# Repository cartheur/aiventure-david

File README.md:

## aiventure-david

Most complex implementation of the animals and emotional toys interactive codebases. A directly-embodied form is [joi](https://github.com/cartheur-joi/arthur-bipedal). Source code in-process of development where our specialized RL rules

* [ideal](https://github.com/cartheur/ideal)
* [haden](https://github.com/ai-haden/aiventure-haden).

_Background_

This project is a 3D-Printed bipedal robot that servers as a platform for _aeon_. It is the third-generation and the most ambitious of our embodied works. The project evolved from:

* The smartphone (2005 - 2016)
* A [toy bear](https://github.com/cartheur/henry) (2016 - 2018)
* A [Nao implementation](https://rumble.com/c/c-2434744) purely as an _aeon personality_ (2017 - 2020)
* A plush [emotional toy](https://emotional.toys) (2017 - 2019)
* An environmentally-friendly [bipedal robot](https://github.com/cartheur/aiventure-david) (2020 - Present)

Here is what it sees

And is evolving into:

* Head redesign for the bipedal robot using the native code files from Poppy but advancing using Solidworks. This head will encapsulate a Liva minicomputer. (Started October 2022)
* Battery compartment and battery to remove the plugged-in power supply. It does run on a 40Ah cell but is pretty power thirsty, even while idle. (Scheduled October 2023)
* De-evolution to a 4.3" HDMI touch screen to link with odroid XU-4, sold by [waveshare](https://www.waveshare.com/4.3inch-HDMI-LCD-B.htm)
    - Problem is: The screen is bloody annoying as it seems to splay one's face with juicy radiation. I was right not considering these kinds of interfaces previously. Bipedal only has a camera and this will stay for the moment. (April 2024)
    - People shoudn't (and certainly aren't) fucking spoiled about a robot having a face. Show me one in manufacture or proposal _right now_.

The complexity of behaviour and implementation is arbitrary. Here at the Generation-Three of the work, currently what is necessary is a stationary test as I complete some animation-training code. I will describe this is in greater detail later. Key is to be able to create my own stuctures and application behaviours outside of the dictations of a compiler - herein lies the direct challenge.

Here is it running (on battery) taking a picture of m.e.

As it is stupid to have a bipedal robot friend attached to cables, the david prototype is at the point where I am starting to test operation with a battery. This battery is rather large (200mm x 150mm x 30mm) at 1.16kg but will run 12 volts to a level of 40Ah. Stationary tests indicate the battery will last 2.5 hours but the next steps will be standing and animation training tests.

As I did work on wireless power, it is a feature to leverage a wireless-charged battery so that the battery could be, say, in a backpack and recharged with a pad, rather than cables. There are some manufacturers working on this but currently it is just wireless-powering phones. Time will tell!

### What does the name of the project mean?

The term *aiventure* means "adventure in AI". The addition of the suffix *david* I don't readily recall, but it is between one of these three _davids_, although it could be more conspiratorial than that:

This david,...

this david, or,...

this david.

#### Errata

Apart from narratives that exclude everyone from building, the build is the thing and the thing alone.

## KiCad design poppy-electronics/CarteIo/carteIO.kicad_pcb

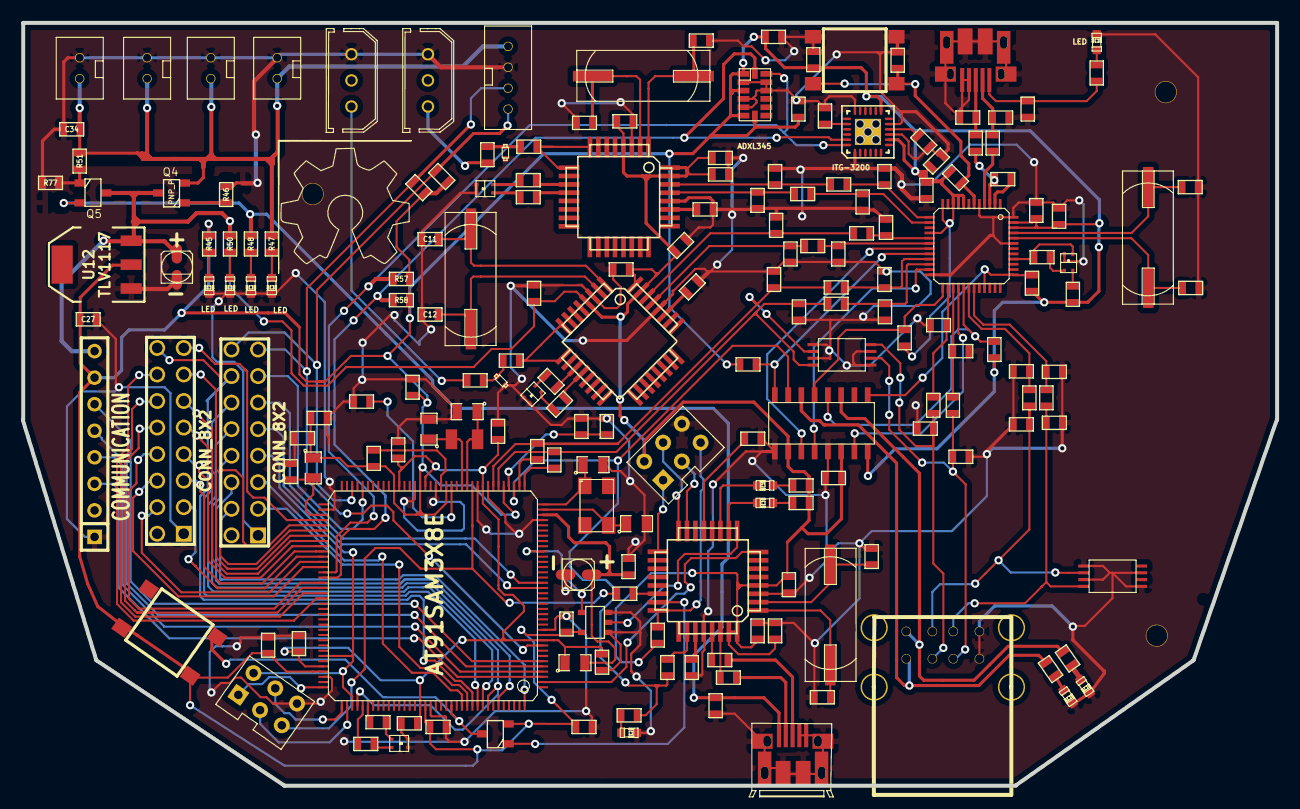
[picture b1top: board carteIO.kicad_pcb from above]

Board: 2 copper layers, 120.0 x 73.0 mm, 195 parts (0 on the bottom side), 156 nets.

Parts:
C1, C2, C61, C62: 22p; SM0603_Capa
C3, C5: 27p; SM0603_Capa
C4, C16, C19, C37, C42, C43, C44, C45, C46, C47, C48, C49, C50, C51, C52, C53, C54, C64, C65, C66, C67, C71: 100n; SM0603_Capa
C6, C7, C8, C9, C14, C15, C17, C20, C28, C29, C59: 22pF; SM0603_Capa
C10, C55: 10u; CAN_RADIAL-CMS
C11, C12, C21, C22: 18p; SM0603_Capa
C13, C23, C38, C63: 1u; SM0603_Capa
C18, C24, C34, C35, C36, C68, C69, C70: 4.7u; SM0603_Capa
C25, C26: 0.1u; SM0603_Capa
C27: 22uF; SM0603_Capa
C39: 10n 4V; SM0603_Capa
C40: 100n 4V; SM0603_Capa
C41: 2.2n 50V; SM0603_Capa
C56, C57, C58, C60: 4.7p; SM0805
C72: 100n 2V; SM0603_Capa
D1, D11: 5.1V; VMD2
D2, D3, D4, D5, D6, D10, D12, D13, D14, D15: LED; LED-0603
FB1, FB2: FILTER; SM0805
J1, J2: UUSB; microUSB
K1, K2: CONN_3; Molex-3-Broches
P1, P4, P5, P9: CONN_2; JST2_TV
P2, P3: CONN_6; HE10-6C
P6, P7: CONN_8X2; pin_array_8x2
P8: COMMUNICATION; SIL-8
P10: CONN_4; JST4_TV
Q1, Q2: 16MHz; HC-49
Q3: 6MHz; HC-49
Q4, Q5: PNP_P; SOT23
Q6: MOS_P2; SOT23
R1, R2, R5, R6, R7, R8, R9, R10, R17, R18, R33, R34: 27R; SM0603
R3: 1.5k; SM0603
R4, R54, R65, R67, R68: 10k; SM0603
R11, R12, R21, R22, R35, R36: R; SM0603
R13, R15, R16, R23, R25, R26, R45: 150; SM0603
R19, R20, R27, R28, R29, R30, R31, R32, R39, R40: 15k; SM0603
R46, R51, R66: 1k; SM0603
R47, R48, R49, R50, R71, R72, R73, R75, R76: 330; SM0603
R52, R53: 39R 1%; SM0603
R55, R56, R57, R58: 2.2k; SM0603
R59: 0; SM0603
R62: 6k8 1%; SM0603
R63, R64, R69, R70: 22R; SM0603
R77: 100k; SM0603
SAM3X8E1: AT91SAM3X8E; LQFP144
SW1, SW2: SW_PUSH; SW_PUSH_SMD
TH1, TH11: 100; SM0603
U1, U3: ATMEGA32U2; TQFP32
U2, U4, U10, U20: LED-BICOLORE; Led_Bicolore
U5: TUSB2077; LQFP48_perso
U6: TPS2044; SOIC16
U8, U9: SN75240; TSSOP8
U11: USB*2
U12: TLV1117; SOT223
U14: ITG-3200; QFN24
U18: ATMEGA16U2; TQFP32
U19: SN74LVC1G125; SOT23-5
U21: ADXL345; LGA14
X1: 12MHz; CRYSTAL_ABM3C
X2: 32kHz; CM315
X3: 16MHz; HC-49
hole-2mm, hole-2mm#2, hole-2mm#3: VAL**; hole-2mm

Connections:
/Alim/3.3V: C27.1, C37.1, C38.1, C39.1, C40.1, C42.1, C43.1, C44.1, C46.1, C47.1, C49.1, C67.1, C68.1, C69.1, C70.1, FB1.1, P8.7, Q6.2, R4.2, R11.2, R12.2, R21.2, R22.2, R36.1, R45.1, R54.1, R55.2, R56.2, R57.2, R58.2, SAM3X8E1.11, SAM3X8E1.41, SAM3X8E1.52, SAM3X8E1.57, SAM3X8E1.62, SAM3X8E1.105, SAM3X8E1.125, SW2.2, U5.8, U5.9, U5.10, U5.12, U5.16, U5.46, U5.47, U6.8, U12.2, U14.8, U14.13, U19.5, U21.1, U21.3, U21.6, U21.7
/Alim/5V: C10.1, C16.1, C18.1, C19.1, C24.1, C25.1, C26.1, C64.1, C65.1, C66.1, C71.1, P3.2, P8.8, Q4.3, Q5.3, R50.1, R65.1, R69.1, R70.1, U1.4, U1.31, U1.32, U3.4, U3.31, U3.32, U6.2, U6.6, U12.3, U18.4, U18.31, U18.32
/Arduino/AI0: P7.13, SAM3X8E1.78
/Arduino/AI1: P7.11, SAM3X8E1.79
/Arduino/AI2: P7.9, SAM3X8E1.80
/Arduino/AI3: P7.7, SAM3X8E1.81
/Arduino/AI4: P7.5, SAM3X8E1.82
/Arduino/AI5: P7.3, SAM3X8E1.83
/Arduino/AI6: P7.4, SAM3X8E1.84
/Arduino/AI7: P7.6, SAM3X8E1.85
/Arduino/AI8: P7.8, SAM3X8E1.88
/Arduino/AI9: P7.10, SAM3X8E1.89
/Arduino/AI10: P7.12, SAM3X8E1.90
/Arduino/AI11: P7.14, SAM3X8E1.91
/Arduino/AVREF: C52.1, FB1.2, SAM3X8E1.75
/Arduino/D+: R9.2, R29.1, R53.1, SAM3X8E1.42, U8.8
/Arduino/D+prog: J2.3, R63.1
/Arduino/D-: R10.2, R30.1, R52.1, SAM3X8E1.43, U8.6
/Arduino/D-prog: J2.2, R64.2
/Arduino/DAC0: P7.15, SAM3X8E1.76
/Arduino/DAC1: P7.16, SAM3X8E1.77
/Arduino/ERASE: Q6.3, SAM3X8E1.130, SW2.1
/Arduino/LED1: R76.1, SAM3X8E1.113
/Arduino/LED2: R75.1, SAM3X8E1.114
/Arduino/MISO: P2.1, SAM3X8E1.108
/Arduino/MOSI: P2.4, SAM3X8E1.109
/Arduino/NCPSO: P2.2, P6.7, SAM3X8E1.102, SAM3X8E1.111
/Arduino/PWM2: P6.4, SAM3X8E1.144
/Arduino/PWM3: P6.6, SAM3X8E1.139
/Arduino/PWM4: P6.8, SAM3X8E1.112, SAM3X8E1.137
/Arduino/PWM5: P6.10, SAM3X8E1.136
/Arduino/PWM6: P6.12, SAM3X8E1.135
/Arduino/PWM7: P6.14, SAM3X8E1.134
/Arduino/PWM8: P6.3, SAM3X8E1.133
/Arduino/PWM9: P6.5, SAM3X8E1.132
/Arduino/PWM11: P6.9, SAM3X8E1.20
/Arduino/PWM12: P6.11, SAM3X8E1.21
/Arduino/PWM13: P6.13, SAM3X8E1.68
/Arduino/PWR: R66.1, R71.1, SAM3X8E1.39, U6.15
/Arduino/RX1: P8.3, SAM3X8E1.3
/Arduino/RX2: P8.5, SAM3X8E1.5
/Arduino/SCL: R58.1, SAM3X8E1.87, U14.23, U21.14
/Arduino/SCLK: P2.3, SAM3X8E1.110
/Arduino/SDA: R57.1, SAM3X8E1.86, U14.24, U21.13
/Arduino/TST: R59.1, SAM3X8E1.51
/Arduino/TX1: P8.4, SAM3X8E1.4
/Arduino/TX2: P8.6, SAM3X8E1.6
/Arduino/VBG: C59.1, R62.1, SAM3X8E1.40
/Arduino/VDDOUT: C45.1, C48.1, C50.1, C51.1, C53.1, FB2.1, SAM3X8E1.10, SAM3X8E1.45, SAM3X8E1.56, SAM3X8E1.61, SAM3X8E1.104, SAM3X8E1.124
/Arduino/VDDPLL: C54.1, C55.1, FB2.2, SAM3X8E1.34
/Arduino/XIN: C56.1, SAM3X8E1.36, X1.1
/Arduino/XIN32: C58.1, SAM3X8E1.48, X2.1
/Arduino/XOUT: C57.1, SAM3X8E1.35, X1.3
/Arduino/XOUT32: C60.1, SAM3X8E1.49, X2.2
/Arduino/programmation/EraseCMD: Q6.1, U18.23
/Arduino/programmation/MISO: P3.1, U18.17
/Arduino/programmation/MOSI: P3.4, U18.16
/Arduino/programmation/RX ATMEGA: SAM3X8E1.2, U18.8
/Arduino/programmation/Reset: P3.5, R65.2, U18.24
/Arduino/programmation/ResetCMD: P2.5, R67.1, SAM3X8E1.47
/Arduino/programmation/SCK: P3.3, U18.15
/Arduino/programmation/TX ATMEGA: SAM3X8E1.27, U19.4
/USB2AX2/D+1: R5.2, R19.1, U1.29
/USB2AX2/D-1: R6.2, R20.1, U1.30
/USB2AX/D+: R7.2, R27.1, U3.29
/USB2AX/D-: R8.2, R28.1, U3.30
/USBHUB/D+hub: C1.1, J1.3, R1.1
/USBHUB/D-hub: C2.1, J1.2, R2.1
/USBHUB/USBFilter/DM0: R2.2, U5.4
/USBHUB/USBFilter/DM1: C7.1, R6.1, U5.13
/USBHUB/USBFilter/DM2: C9.1, R8.1, U5.17
/USBHUB/USBFilter/DM3: C15.1, R10.1, U5.21
/USBHUB/USBFilter/DM4: C20.1, R18.1, U5.26
/USBHUB/USBFilter/DM5: C29.1, R34.1, U5.30
/USBHUB/USBFilter/DP0: R1.2, R3.2, U5.3
/USBHUB/USBFilter/DP1: C6.1, R5.1, U5.14
/USBHUB/USBFilter/DP2: C8.1, R7.1, U5.18
/USBHUB/USBFilter/DP3: C14.1, R9.1, U5.22
/USBHUB/USBFilter/DP4: C17.1, R17.1, U5.27
/USBHUB/USBFilter/DP5: C28.1, R33.1, U5.31
/USBHUB/hubstatus: R35.1, U5.40, U10.4
/connector out/5V: C34.1, P1.1, P4.1, P5.1, P9.1, P10.1, Q4.2, R47.1, R51.1
/connector out/D+Bot: R33.2, R39.1, U9.8, U11.6
/connector out/D+Top: R17.2, R31.1, U8.2, U11.5
/connector out/D- Top: R18.2, R32.1, U8.4, U11.3
/connector out/D-Bot: R34.2, R40.1, U9.6, U11.4
/connector out/PWR Bot: R73.1, U6.11, U11.2
/connector out/PWR Top: R72.1, U6.14, U11.1
/connector out/SCL: P6.16, P10.4, R56.1, SAM3X8E1.70
/connector out/SDA: P6.15, P10.3, R55.1, SAM3X8E1.9
/connectorIn/Vhub: C36.1, J1.1, R49.1
/connectorIn/Vprog: C35.1, J2.1, Q5.2, R48.1
GND: C1.2, C2.2, C3.2, C4.1, C5.2, C6.2, C7.2, C8.2, C9.2, C10.2, C11.2, C12.2, C13.2, C14.2, C15.2, C16.2, C17.2, C18.2, C19.2, C20.2, C21.2, C22.2, C23.2, C24.2, C25.2, C26.2, C27.2, C28.2, C29.2, C34.2, C35.2, C36.2, C37.2, C38.2, C39.2, C40.2, C41.2, C42.2, C43.2, C44.2, C45.2, C46.2, C47.2, C48.2, C49.2, C50.2, C51.2, C52.2, C53.2, C54.2, C55.2, C56.2, C57.2, C58.2, C59.2, C60.2, C61.2, C62.2, C63.2, C64.2, C65.2, C66.2, C67.2, C68.2, C69.2, C70.2, C71.2, C72.2, D1.1, D2.2, D3.2, D4.2, D5.2, D6.2, D11.1, D13.2, D14.2, D15.2, J1.4, J1.5, J2.4, J2.5, K1.1, K2.1, P1.2, P2.6, P3.6, P4.2, P5.2, P6.1, P7.1, P8.1, P9.2, P10.2, R19.2, R20.2, R27.2, R28.2, R29.2, R30.2, R31.2, R32.2, R39.2, R40.2, R46.2, R59.2, R62.2, R68.1, R77.2, SAM3X8E1.12, SAM3X8E1.33, SAM3X8E1.44, SAM3X8E1.46, SAM3X8E1.54, SAM3X8E1.58, SAM3X8E1.74, SAM3X8E1.106, SAM3X8E1.126, SW1.1, U1.3, U1.28, U2.3, U2.4, U3.3, U3.28, U4.3, U4.4, U5.5, U5.24, U5.43, U5.48, U6.1, U6.5, U8.1, U8.3, U8.5, U8.7, U9.1, U9.3, U9.5, U9.7, U10.3, U11.7, U11.8, U12.1, U14.1, U14.9, U14.11, U14.18, U18.3, U18.28, U19.1, U19.3, U20.3, U20.4, U21.2, U21.4, U21.5, U21.11, U21.12
unnamed: D11.2, R13.1, TH11.1
unnamed: C13.1, U3.27
unnamed: R16.1, U3.12
unnamed: R16.2, U4.1
unnamed: R15.1, U4.2
unnamed: K2.3, TH11.2
unnamed: C12.1, Q1.2, U3.2
unnamed: C11.1, Q1.1, U3.1
unnamed: R15.2, U3.11
unnamed: R13.2, U3.8, U3.9
unnamed: C23.1, U1.27
unnamed: C21.1, Q2.1, U1.1
unnamed: D1.2, R23.1, TH1.1
unnamed: R26.2, U2.1
unnamed: R25.2, U1.11
unnamed: R26.1, U1.12
unnamed: K1.3, TH1.2
unnamed: R25.1, U2.2
unnamed: R23.2, U1.8, U1.9
unnamed: C22.1, Q2.2, U1.2
unnamed: R3.1, U5.2
unnamed: C4.2, R4.1, SW1.2, U5.6
unnamed: U5.28, U6.7
unnamed: U5.23, U6.4
unnamed: D15.1, R73.2
unnamed: D13.1, R71.2
unnamed: R11.1, U5.20, U6.16
unnamed: R21.1, U5.29, U6.12
unnamed: R35.2, U10.1
unnamed: U5.19, U6.3
unnamed: R12.1, U5.25, U6.13
unnamed: R22.1, U5.33, U5.37, U6.9
unnamed: C3.1, Q3.1, U5.45
unnamed: C5.1, Q3.2, U5.44
unnamed: R36.2, U10.2
unnamed: D14.1, R72.2
unnamed: D2.1, R45.2
unnamed: R52.2, SAM3X8E1.38
unnamed: R53.2, SAM3X8E1.37
unnamed: R54.2, SAM3X8E1.53
unnamed: R75.2, U20.1
unnamed: R76.2, U20.2
unnamed: C41.1, U14.20
unnamed: C72.1, U14.10
unnamed: D6.1, R50.2
unnamed: D5.1, R49.2
unnamed: D4.1, R48.2
unnamed: D3.1, R47.2
unnamed: Q5.1, R51.2, R77.1
unnamed: Q4.1, R46.1
unnamed: D12.1, R70.2
unnamed: D10.1, R69.2
unnamed: C63.1, U18.27
unnamed: D12.2, U18.10
unnamed: D10.2, U18.11
unnamed: C61.1, U18.1, X3.1
unnamed: R63.2, U18.29
unnamed: U18.9, U19.2
unnamed: R66.2, U18.26
unnamed: R68.2, U18.13
unnamed: R67.2, U18.22
unnamed: R64.1, U18.30
unnamed: C62.1, U18.2, X3.2

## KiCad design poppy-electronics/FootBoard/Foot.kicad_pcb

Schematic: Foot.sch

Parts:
Nano1: ARDUINO_NANO
P1, P2: CONN_2
P3, P4: CONN_6
R1, R2, R3, R4, R6, R7: PR
Source1, Source2, Source3, Source5, Source6, Source7: CURRENTSOURCE

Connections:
+5V: Nano1.19 (+5V), P1.1, R1.1, R2.1, R3.1, R4.1, R6.1, R7.1, Source1.5 (Vs), Source2.5 (Vs), Source3.5 (Vs), Source5.5 (Vs), Source6.5 (Vs), Source7.5 (Vs)
/A0: Nano1.27 (A0), P4.6
/A1: Nano1.26 (A1), P4.5
/A2: Nano1.25 (A2), P4.4
/A3: Nano1.24 (A3), P4.3
/A6: Nano1.21 (A6), P4.2
/A7: Nano1.20 (A7), P4.1
/RA0: P3.6, Source1.2 (IOUT)
/RA1: P3.5, Source2.2 (IOUT)
/RA2: P3.4, Source3.2 (IOUT)
/RA3: P3.3, Source5.2 (IOUT)
/RA6: P3.2, Source6.2 (IOUT)
/RA7: P3.1, Source7.2 (IOUT)
/SCL: Nano1.22 (A5/SCL), P2.1
/SDA: Nano1.23 (A4/SDA), P2.2 (PM)
GND: Nano1.4 (GND), Nano1.17 (GND), P1.2 (PM), Source1.3 (GND), Source2.3 (GND), Source3.3 (GND), Source5.3 (GND), Source6.3 (GND), Source7.3 (GND)
unnamed: R6.2, Source6.4 (Rext)
unnamed: R7.2, Source7.4 (Rext)
unnamed: R4.2, Source5.4 (Rext)
unnamed: R3.2, Source3.4 (Rext)
unnamed: R2.2, Source2.4 (Rext)
unnamed: R1.2, Source1.4 (Rext)

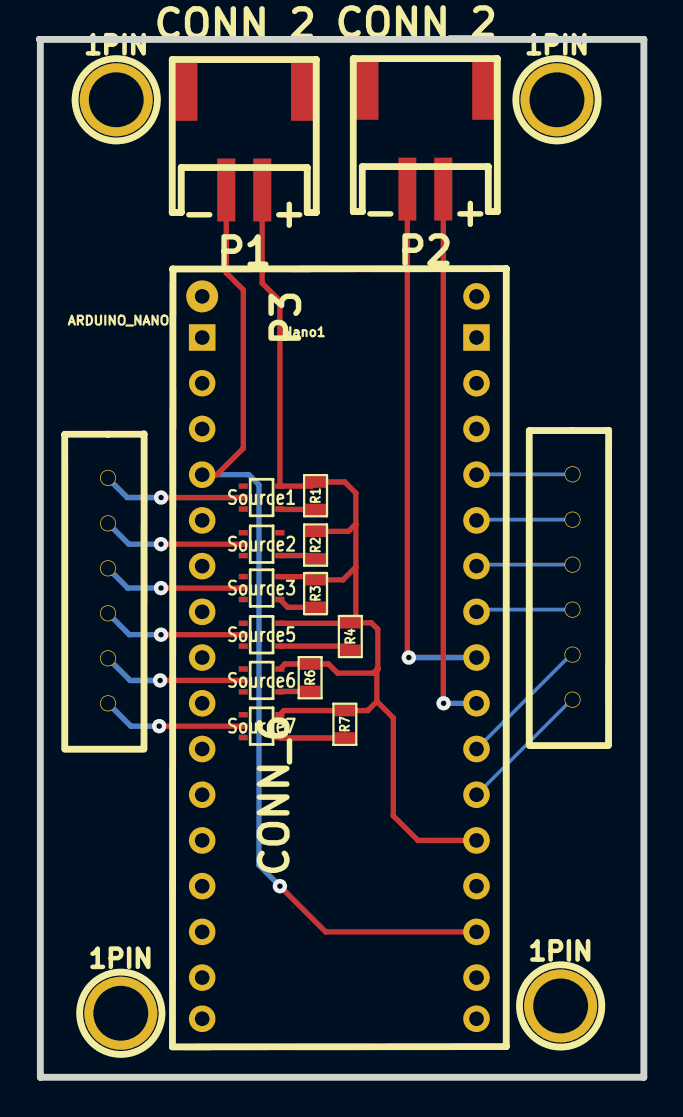
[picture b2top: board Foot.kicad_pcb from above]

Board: 2 copper layers, 33.6 x 57.7 mm, 21 parts (0 on the bottom side), 22 nets.

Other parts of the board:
1PIN, 1PIN#2, 1PIN#3, 1PIN#4: P***; 1pin

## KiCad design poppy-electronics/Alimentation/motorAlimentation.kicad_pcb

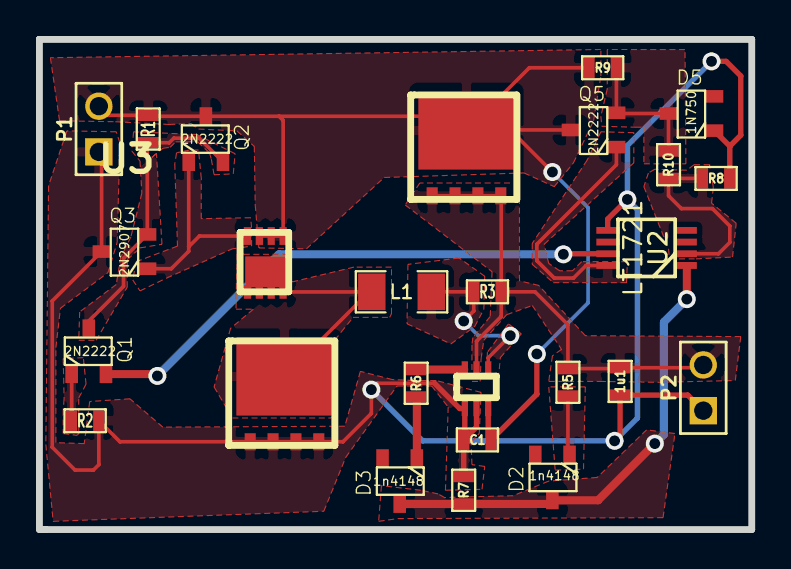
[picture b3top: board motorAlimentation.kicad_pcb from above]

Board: 2 copper layers, 39.6 x 27.2 mm, 26 parts (0 on the bottom side), 16 nets.

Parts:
1u1: 100nF; SM0603_Capa
C1: 100nF; SM0603_Capa
D1, D4: MBRB2545CT; PowerFlat
D2, D3: 1n4148; SOT23D
D5: 1N750; SOT23D
L1: 4.7u_6.4m; SM1206
P1, P2: CONN_2; PIN_ARRAY_2X1
Q1, Q2, Q5: 2N2222; SOT23
Q3: 2N2907; SOT23
R1: 1k; SM0603_Resistor
R2: 330; SM0603_Resistor
R3: 15m; SM0603_Resistor
R5: 49.3k; SM0603
R6, R7, R8, R10: 10k; SM0603
R9: 4.7k; SM0603
U1: INA213; DCK
U2: LT1721; MSOP_8
U3: MOSP_PWF; PowerPAK

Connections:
/14V_-_10A: 1u1.2, D4.1, P2.2, R3.2, R5.2, U1.5
/Vin: C1.2, D4.2, P1.2, Q2.3, Q5.3, R1.1, R9.1, U1.3, U3.1, U3.2, U3.3
/outINA: R6.2, U1.6
GND: 1u1.1, C1.1, D1.1, D5.1, P1.1, P2.1, Q3.3, R2.2, R7.2, R8.1, U1.1, U1.2, U2.5
unnamed: D3.1, R6.1
unnamed: D2.1, R5.1
unnamed: Q1.3, Q2.2, Q3.2, R1.2
unnamed: D1.2, L1.1, U3.5
unnamed: Q1.1, R2.1
unnamed: Q5.1, U2.8
unnamed: L1.2, R3.1, U1.4
unnamed: D5.2, Q5.2, R9.2, R10.2
unnamed: Q2.1, Q3.1, U3.4
unnamed: Q1.2, U2.7
unnamed: D2.2, D3.2, R7.1, U2.1
unnamed: R8.2, R10.1, U2.2

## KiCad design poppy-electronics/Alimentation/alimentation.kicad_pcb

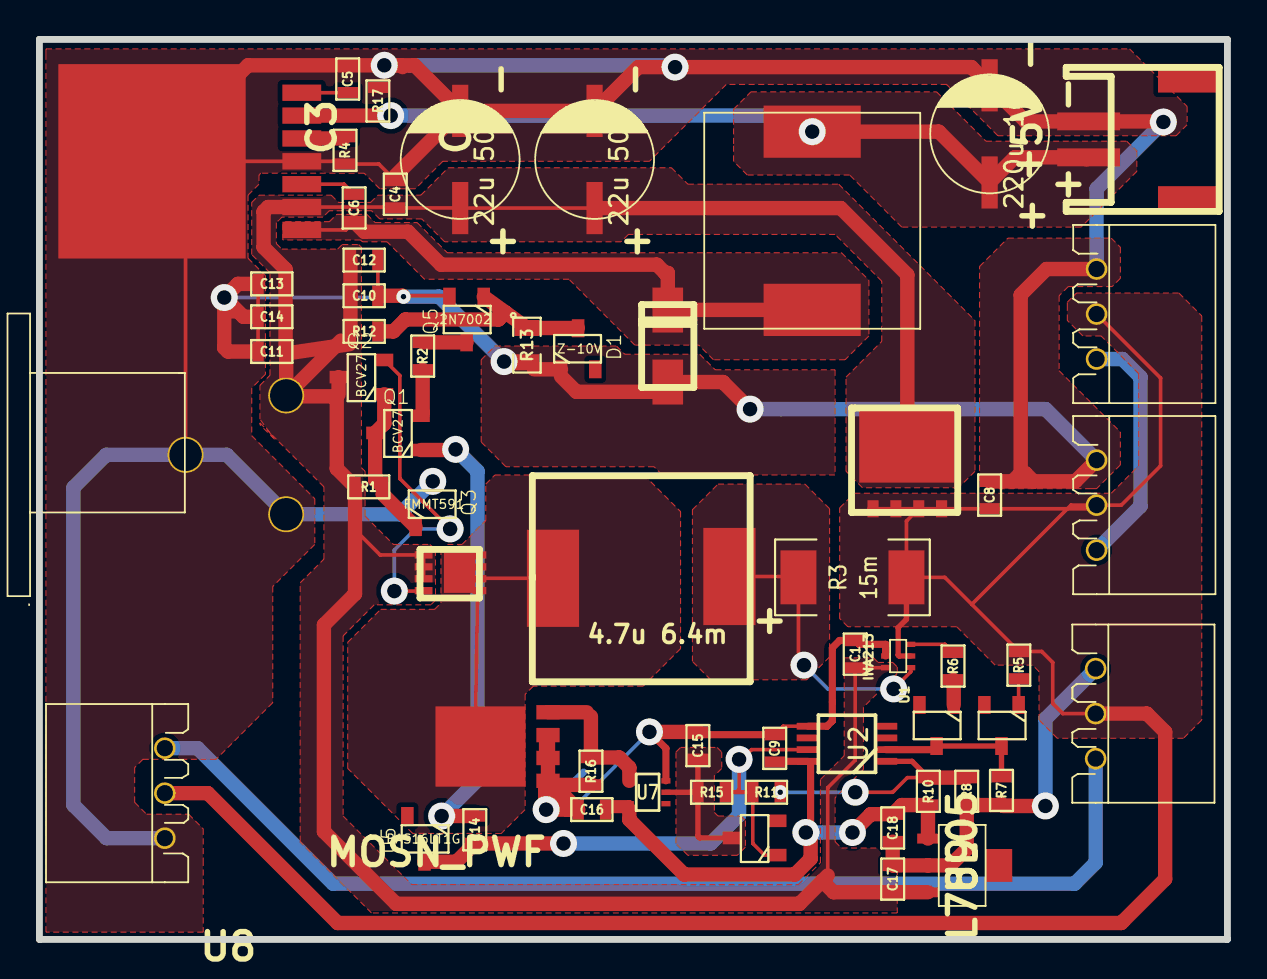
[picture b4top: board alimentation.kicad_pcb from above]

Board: 2 copper layers, 66.0 x 50.0 mm, 60 parts (0 on the bottom side), 27 nets.

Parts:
+5V: CONN_2; CONN_JST-2_SMD
C1, C5, C9, C16, C18: 100n; SM0603
C2, C3: 22u 50V; CAN-Radial-D8
C4: 470n; SM0603
C6: 10n; SM0603
C7: 220u 16V; CAN-Radial-D8
C8: 20u; SM0603
C10, C11, C12, C13, C14: 4.7u; SM0603
C15: 470p; SM0603
C17: 330n; SM0603
D1: Z-10V; SOT23D
D2, D3: BAS16LT1G; SOT23D
D4: STPS3045DJF; PowerFlat
D6: B350A-13-F; DO-214AC
K1, K2, K3, K4: CONN_3; Molex3B_90
L1: 4.7u 6.4m; Inductor1210
L2: 33u; L-12-12-10
P4: CONN_2; JACK_Puissance
Q1, Q2: BCV27; SOT23_p
Q3: FMMT591; SOT23_p
Q5: 2N7002; SOT23
R1, R12, R14, R15, R17: 1k; SM0603
R2: 330; SM0603
R3: 15m; SM2512
R4: 8.2k; SM0603
R5: 49.3k; SM0603
R6, R7, R8, R10, R16: 10k; SM0603
R11: 470k; SM0603
R13: 3k; SM0805
U1: INA213; SC70
U2: LT1721; MSOP_8
U3: SI7101DN-T1-GE3; PowerPAK
U4: LM2673; TO263
U5, U6: BAS16LT1G; SOT23
U7: 74HC1G14; SOT353
U8: MOSN_PWF; PG-TDSON
U9: L78L05; SOT-89

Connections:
+5V: C9.2, C16.2, C18.1, R10.2, U2.8, U7.5, U9.1
/Connector In/Stabilized: C1.2, C2.1, C3.1, C4.1, C10.1, C11.1, C12.1, C13.1, C14.1, C17.1, D4.2, P4.1, Q2.3, R1.1, R12.1, U1.3, U3.1, U3.2, U3.3, U4.2, U9.3
/Motor Alimentation/cmdNmos: R16.2, U7.4, U8.4
/Motor Alimentation/outINA: R6.2, U1.6
/connector Out/5V: +5V.1, C7.1, L2.2, R17.2, U4.6
/connector Out/14V: C8.2, D4.1, K1.2, K2.2, K3.2, K4.2, R3.2, R5.2, U1.5
/connector Out/Data: K1.3, K2.3
/connector Out/Data2: K3.3, K4.3
GND: +5V.2, C1.1, C2.2, C3.2, C4.2, C5.2, C7.2, C8.1, C9.1, C10.2, C11.2, C12.2, C13.2, C14.2, C15.1, C16.1, C17.2, C18.2, D1.1, D6.1, K1.1, K2.1, K3.1, K4.1, P4.2, Q3.3, Q5.2, R4.2, R7.2, R8.1, R13.2, R16.1, R17.1, U1.1, U1.2, U2.5, U4.4, U4.8, U7.3, U8.1, U8.2, U8.3, U9.2
unnamed: Q1.1, R14.1, U5.1
unnamed: Q1.3, Q2.1, Q3.1, R1.2
unnamed: Q1.2, R2.1
unnamed: L1.2, R3.1, U1.4
unnamed: D1.2, Q5.1, R12.2, R13.1
unnamed: L1.1, U3.5, U8.5
unnamed: Q2.2, Q3.2, U3.4
unnamed: D2.2, D3.2, R7.1, U2.2
unnamed: D3.1, R6.1
unnamed: R8.2, R10.1, R11.2, U2.1
unnamed: D2.1, R5.1
unnamed: Q5.3, R2.2
unnamed: R11.1, R14.2, R15.1, U2.7, U5.3, U6.1
unnamed: C15.2, R15.2, U6.3, U7.2
unnamed: C5.1, U4.7
unnamed: C6.1, U4.3
unnamed: C6.2, D6.2, L2.1, U4.1
unnamed: R4.1, U4.5

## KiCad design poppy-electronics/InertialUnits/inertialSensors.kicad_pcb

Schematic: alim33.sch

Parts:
C10: 10u
C27: 22uF
D2: LED
R45: 150
U1: TLV1117

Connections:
/Connector/3.3V: C27.1, R45.1, U1.2 (Vout); also elsewhere on the board
/Connector/alim 3.3/5V: C10.1, U1.3 (Vin); also elsewhere on the board
GND: C10.2, C27.2, D2.2 (K), U1.1 (GND); also elsewhere on the board
unnamed: D2.1 (A), R45.2

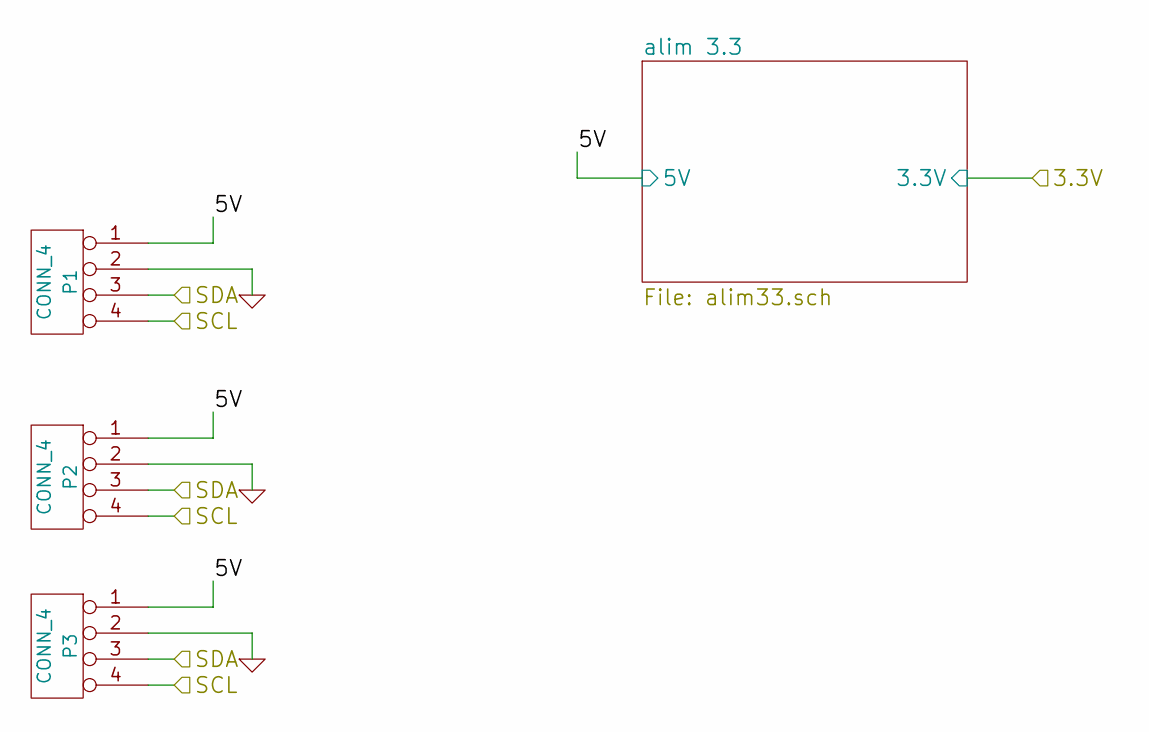
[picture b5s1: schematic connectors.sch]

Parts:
P1, P2, P3: CONN_4

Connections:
/Connector/SCL: P1.4, P2.4, P3.4; also elsewhere on the board
/Connector/SDA: P1.3, P2.3, P3.3; also elsewhere on the board
/Connector/alim 3.3/5V: P1.1, P2.1, P3.1; also elsewhere on the board
GND: P1.2, P2.2, P3.2; also elsewhere on the board

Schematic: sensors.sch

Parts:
C37: 100n
C38: 1u
C39: 10n 4V
C40: 100n 4V
C41: 2.2n 50V
C72: 100n 2V
U14: ITG-3200
U21: ADXL345

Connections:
/Connector/3.3V: C37.1, C38.1, C39.1, C40.1, U14.8 (Vlogic), U14.13 (VDD), U21.1 (VDD_I/O), U21.3 (Reserved), U21.6 (Vs), U21.7 (CS/); also elsewhere on the board
/Connector/SCL: U14.23 (SCL), U21.14 (SCL/SCLK); also elsewhere on the board
/Connector/SDA: U14.24 (SDA), U21.13 (SDA/SDI/SDIO); also elsewhere on the board
GND: C37.2, C38.2, C39.2, C40.2, C41.2, C72.2, U14.1 (CLKIN), U14.9 (AD0), U14.11 (Resv-G), U14.18 (GND), U21.2 (GND), U21.4 (GND), U21.5 (GND), U21.11 (Reserved), U21.12 (SDO/ALT); also elsewhere on the board
unnamed: C72.1, U14.10 (RegOut)
unnamed: C41.1, U14.20 (CPout)

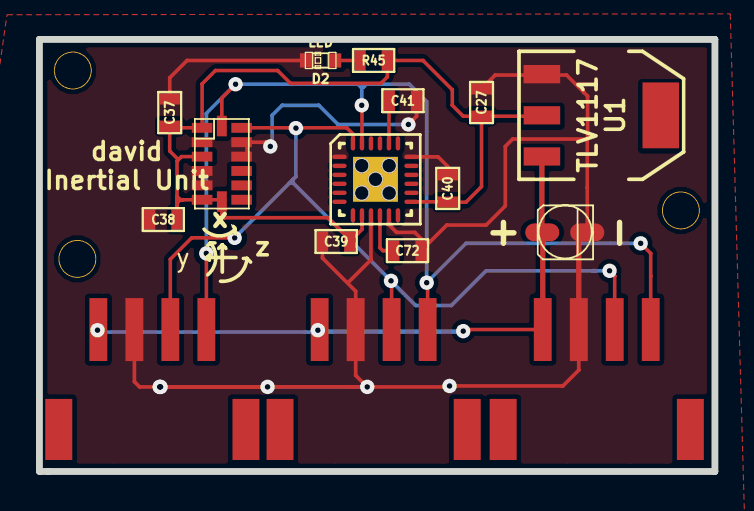
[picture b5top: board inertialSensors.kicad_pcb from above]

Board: 2 copper layers, 37.5 x 24.0 mm, 19 parts (0 on the bottom side), 8 nets.

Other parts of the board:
hole-2mm, hole-2mm#2, hole-2mm#3: VAL**; hole-2mm

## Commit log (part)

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2022-05-02 init: Initial version
2022-05-02 feat: upgrade to KiCad6
2022-11-04 docs: Added context to the story of the repository
2022-11-04 docs: Add content
2022-11-04 docs: Add size control
2022-11-04 fix: Change image sizes
2022-11-04 init: Add print files for FlashForge
2022-11-04 fix: Set davids
2022-11-04 fix: Remove excess bulletpoints
2022-11-04 docs: Set bulletpoints
2022-11-04 fix: Set bulletpoints
2022-11-04 media: Add artwork
2022-11-05 docs: Update media
2022-11-05 docs: Correct description
2022-11-08 docs: Adjust text
2023-02-24 feat: Add RL generic code
2023-02-24 docs: Add torso-motor list
2023-02-24 Staging (#2)
    * feat: upgrade to KiCad6
    * media: Add artwork
    * feat: Add RL generic code
    * docs: Add torso-motor list
    ---------
2023-02-24 docs: Add reference to aiventure-aeon
2023-03-02 Create LICENSE file
2023-03-23 Reformat Unicode
2023-03-23 Clean repository
2023-03-23 Reame folder
2023-03-23 Include backstory of the project
2023-03-23 Add cultural details
2023-03-23 Add relevant cultural detail
2023-03-23 Try text align justify
2023-03-23 Add justified text
2023-03-23 Markdown generic justify text
2023-03-23 Remove justify text
2023-03-23 Add picture of original device to story
2023-03-23 Change image tag
2023-03-23 Reduce image size
2023-03-23 Resize image
2023-03-23 Try justify
2023-03-23 Add html to manage formatting
2023-03-23 Format justify using html
2023-03-23 Justify paragraphs
2023-03-23 Add thesis source
2023-03-23 Remove file
2023-03-23 Add historical writing
2023-03-23 Add work on abstract phrases
2023-03-23 Minor addition
2023-03-23 Add sponsorship possibility to the project
2023-03-23 Add head solidworks files
2023-03-23 Add motor designs
2023-03-23 Clean-up folder
2023-03-23 Add flashforge print files
2023-03-23 Clarify areas of the text
2023-03-23 Clarify text of the backstory
2023-03-23 Expand the backstory
2023-03-23 Foxus worduse
2023-03-23 Split backstory paragraphs
2023-03-23 Clarify parts of the backstory
2023-03-23 Add link to mention
2023-03-23 Add md link format
2023-03-23 Another format
2023-03-23 Clean-up link formatting
2023-03-23 Clarify text association
2023-03-23 Minor text fixes
2023-03-23 Add issues notification
2023-03-26 Add license notification
2023-03-26 Add repo link
2023-03-26 Change license
2023-03-27 Clarify project status
2023-03-27 Move backstory, add evolution elements
2023-03-27 Add media files
2023-03-27 Add new research
2023-03-27 Add further research details
2023-03-27 Add paragraph spacing
2023-03-27 Add clarity to research
2023-03-27 Add research chronology
2023-03-27 Remove pesky bullets
2023-03-27 Clean research text
2023-03-27 Sort battery details
2023-03-27 Add research charging diversity
2023-04-05 Add funding channel
2023-04-09 Add Solidworks design files
2023-04-14 Add to backstory
2023-04-27 Adjust text promotions
2023-06-12 Advance text
2023-06-12 Add project notes
2023-06-12 Expand project scope
2023-06-12 Clarity to descriptive
2023-06-12 Clean dates
2023-06-14 Update notes
2023-06-14 Add redesign files
2023-06-14 Reorganize files and upload new
2023-06-14 Refactor naming
2023-06-14 Reset file
2023-07-24 Add entry
2024-02-22 Add screen sales point.
2024-05-03 Add media
2024-05-03 Add note
2024-05-03 Show media
2024-05-03 Set into motion
2024-05-03 Date assignment
2024-05-03 Add intention
2024-05-06 Add challenge
2024-08-22 Add full-fil;e
2024-08-22 Add full-file
2024-08-23 Add register document
2024-08-24 Making a difference
2025-01-28 Add diagram
2025-01-28 Add notes
2025-01-28 Add disclosure
2025-01-28 Add notification
2025-01-28 Add clarification
2025-01-29 Add haden reference
2025-04-16 Add content
2025-04-19 Add notebook
2025-04-19 Add image
2025-04-19 Add help
2025-04-19 Add readme
